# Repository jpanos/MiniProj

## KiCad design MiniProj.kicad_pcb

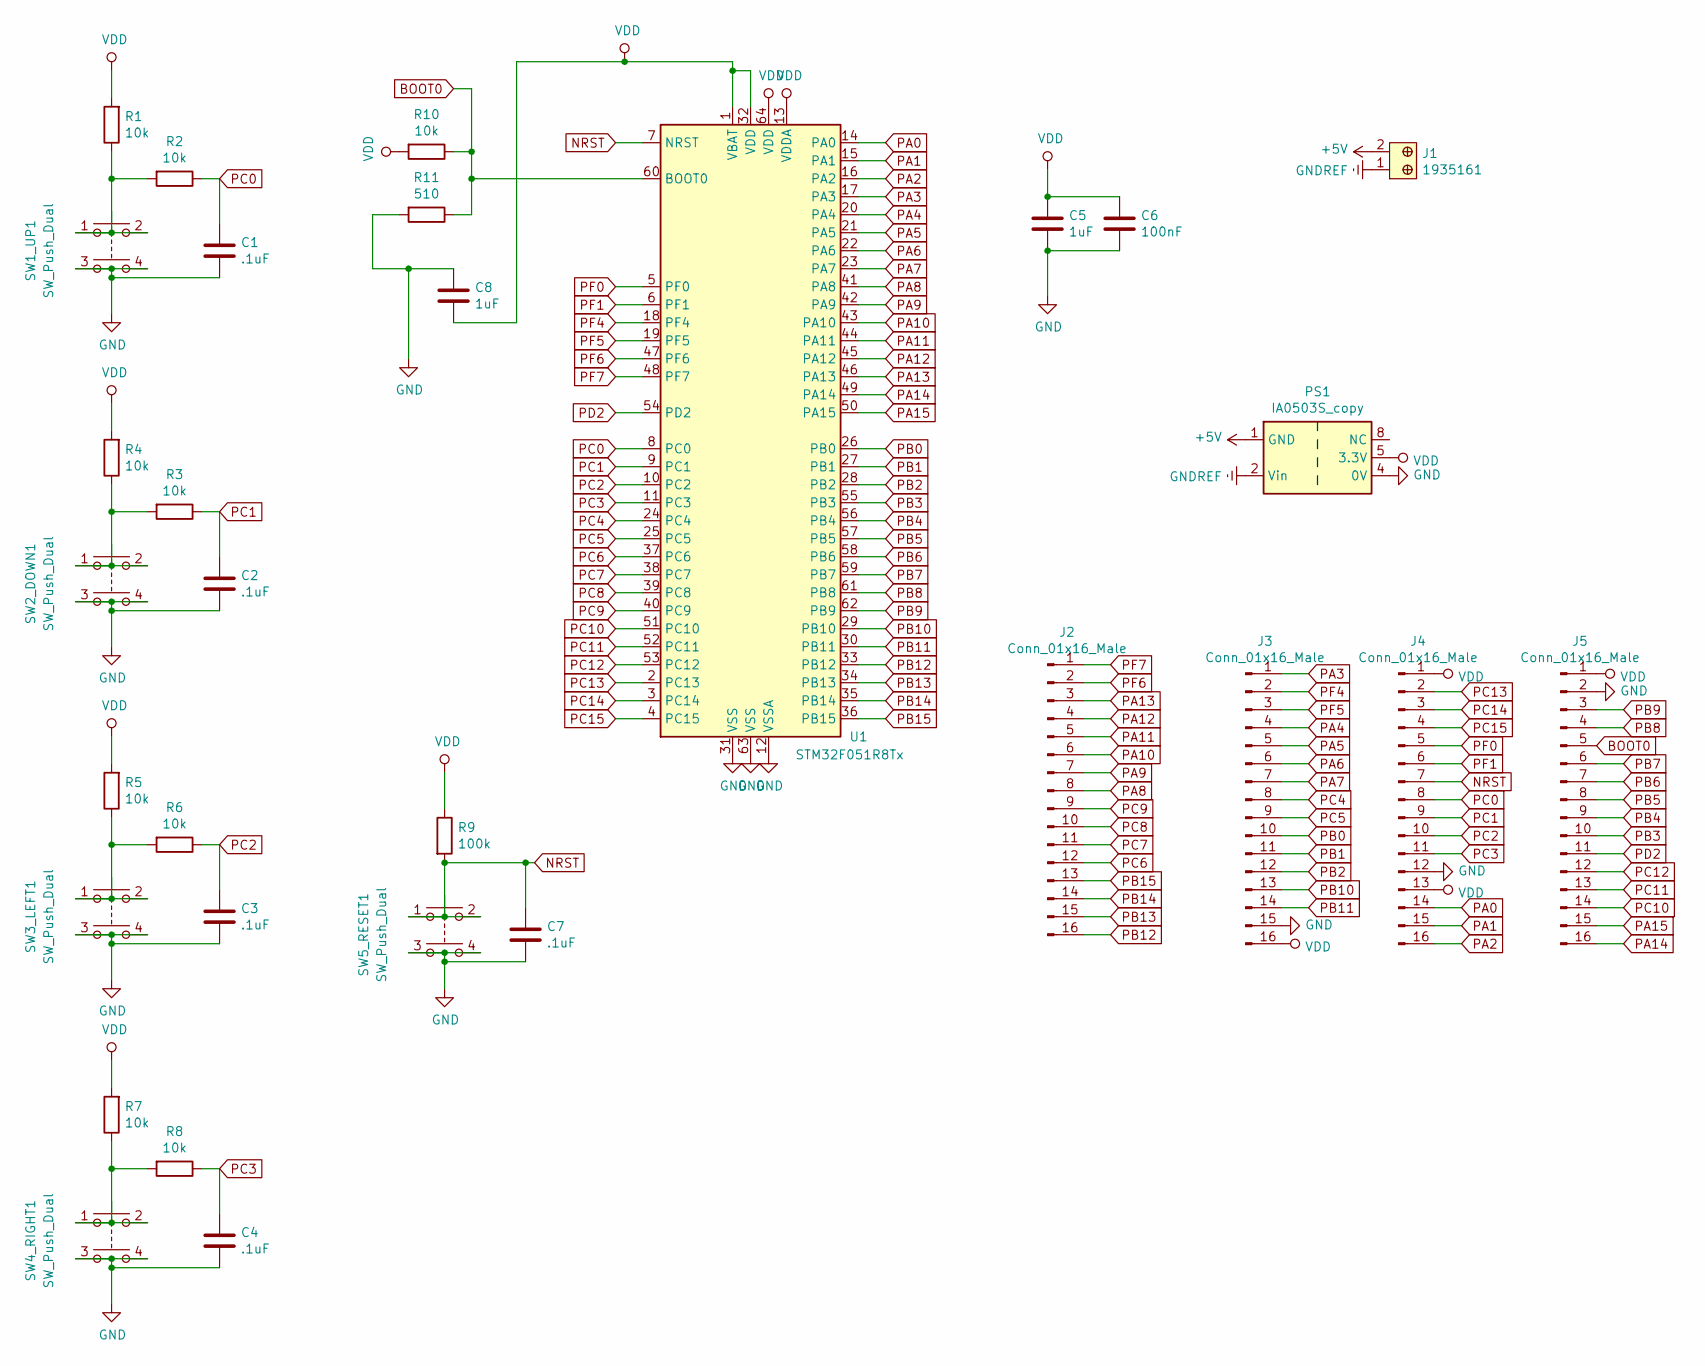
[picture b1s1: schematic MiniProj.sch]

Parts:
C1, C2, C3, C4, C7: .1uF; C_0805_2012Metric_Pad1.15x1.40mm_HandSolder
C5, C8: 1uF; C_0805_2012Metric_Pad1.15x1.40mm_HandSolder
C6: 100nF; C_0805_2012Metric_Pad1.15x1.40mm_HandSolder
J1: 1935161; Terminal_Block_D1.3mm_P5mm; MPN 1935161; Digi-Key_PN 277-1667-ND
J2, J3, J4, J5: Conn_01x16_Male; PinHeader_1x16_P2.54mm_Vertical
PS1: IA0503S_copy; CONV_PDS1-S3-S3-M
R1, R2, R3, R4, R5, R6, R7, R8, R10: 10k; R_0805_2012Metric_Pad1.15x1.40mm_HandSolder
R9: 100k; R_0805_2012Metric_Pad1.15x1.40mm_HandSolder
R11: 510; R_0805_2012Metric_Pad1.15x1.40mm_HandSolder
SW1_UP1, SW2_DOWN1, SW3_LEFT1, SW4_RIGHT1, SW5_RESET1: SW_Push_Dual; SW_TH_Tactile_Omron_B3F-10xx
U1: STM32F051R8Tx; LQFP-64_10x10mm_P0.5mm

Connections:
+5V: J1.2, PS1.1 (GND)
BOOT0: J5.5, R10.1, R11.1, U1.60 (BOOT0)
GND: C1.2, C2.2, C3.2, C4.2, C5.2, C6.2, C7.2, C8.1, J3.15, J4.12, J5.2, PS1.4 (0V), R11.2, SW1_UP1.3, SW1_UP1.4, SW2_DOWN1.3, SW2_DOWN1.4, SW3_LEFT1.3, SW3_LEFT1.4, SW4_RIGHT1.3, SW4_RIGHT1.4, SW5_RESET1.3, SW5_RESET1.4, U1.12 (VSSA), U1.31 (VSS), U1.63 (VSS)
GNDREF: J1.1, PS1.2 (Vin)
NRST: C7.1, J4.7, R9.2, SW5_RESET1.1, SW5_RESET1.2, U1.7 (NRST)
unnamed: R1.1, R2.2, SW1_UP1.1, SW1_UP1.2
unnamed: R3.2, R4.1, SW2_DOWN1.1, SW2_DOWN1.2
unnamed: R5.1, R6.2, SW3_LEFT1.1, SW3_LEFT1.2
unnamed: R7.1, R8.2, SW4_RIGHT1.1, SW4_RIGHT1.2
PA0: J4.14, U1.14 (PA0)
PA1: J4.15, U1.15 (PA1)
PA2: J4.16, U1.16 (PA2)
PA3: J3.1, U1.17 (PA3)
PA4: J3.4, U1.20 (PA4)
PA5: J3.5, U1.21 (PA5)
PA6: J3.6, U1.22 (PA6)
PA7: J3.7, U1.23 (PA7)
PA8: J2.8, U1.41 (PA8)
PA9: J2.7, U1.42 (PA9)
PA10: J2.6, U1.43 (PA10)
PA11: J2.5, U1.44 (PA11)
PA12: J2.4, U1.45 (PA12)
PA13: J2.3, U1.46 (PA13)
PA14: J5.16, U1.49 (PA14)
PA15: J5.15, U1.50 (PA15)
PB0: J3.10, U1.26 (PB0)
PB1: J3.11, U1.27 (PB1)
PB2: J3.12, U1.28 (PB2)
PB3: J5.10, U1.55 (PB3)
PB4: J5.9, U1.56 (PB4)
PB5: J5.8, U1.57 (PB5)
PB6: J5.7, U1.58 (PB6)
PB7: J5.6, U1.59 (PB7)
PB8: J5.4, U1.61 (PB8)
PB9: J5.3, U1.62 (PB9)
PB10: J3.13, U1.29 (PB10)
PB11: J3.14, U1.30 (PB11)
PB12: J2.16, U1.33 (PB12)
PB13: J2.15, U1.34 (PB13)
PB14: J2.14, U1.35 (PB14)
PB15: J2.13, U1.36 (PB15)
PC0: C1.1, J4.8, R2.1, U1.8 (PC0)
PC1: C2.1, J4.9, R3.1, U1.9 (PC1)
PC2: C3.1, J4.10, R6.1, U1.10 (PC2)
PC3: C4.1, J4.11, R8.1, U1.11 (PC3)
PC4: J3.8, U1.24 (PC4)
PC5: J3.9, U1.25 (PC5)
PC6: J2.12, U1.37 (PC6)
PC7: J2.11, U1.38 (PC7)
PC8: J2.10, U1.39 (PC8)
PC9: J2.9, U1.40 (PC9)
PC10: J5.14, U1.51 (PC10)
PC11: J5.13, U1.52 (PC11)
PC12: J5.12, U1.53 (PC12)
PC13: J4.2, U1.2 (PC13)
PC14: J4.3, U1.3 (PC14)
PC15: J4.4, U1.4 (PC15)
PD2: J5.11, U1.54 (PD2)
PF0: J4.5, U1.5 (PF0)
PF1: J4.6, U1.6 (PF1)
PF4: J3.2, U1.18 (PF4)
PF5: J3.3, U1.19 (PF5)
PF6: J2.2, U1.47 (PF6)
PF7: J2.1, U1.48 (PF7)
VDD: C5.1, C6.1, C8.2, J3.16, J4.1, J4.13, J5.1, PS1.5 (3.3V), R1.2, R4.2, R5.2, R7.2, R9.1, R10.2, U1.1 (VBAT), U1.13 (VDDA), U1.32 (VDD), U1.64 (VDD)

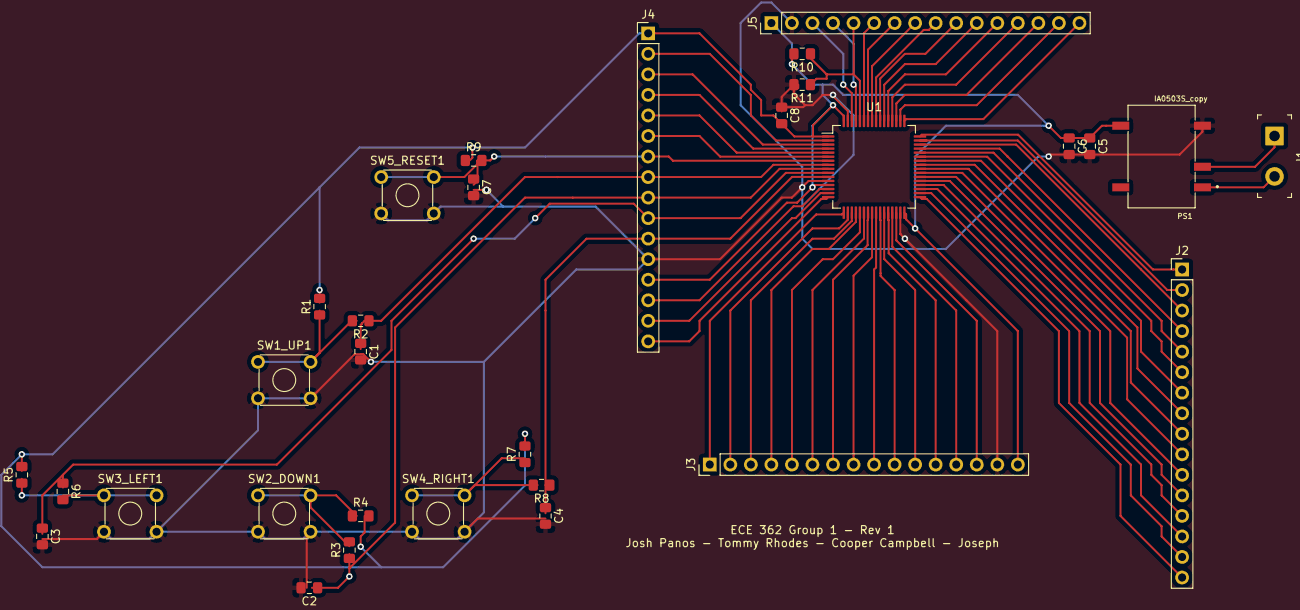
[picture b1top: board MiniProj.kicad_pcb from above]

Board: 2 copper layers, 31 parts (0 on the bottom side), 65 nets.

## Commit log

2019-11-18 Working
    Working
2019-11-19 PLPCB
    Rev 1
2019-11-21 BIgger pads
    Change R and C
2020-09-17 Creation of ECE 477 PCB
    Starting PCB
2020-09-17 Testing
    Testing
2020-09-17 Added 4 LED pads
    Added 4 cirucits for the installation of LEDs still need to calculate the resitance to apply to the LEDs based on colors
